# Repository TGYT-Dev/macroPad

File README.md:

# Images

<p align="left">
  
  <br>

</p>

# Bill of Materials
This should all be iuncluded in the macropad kit.

> 5x Cherry MX Switches
> 
> 1x Alps EC11E Rotary Encoder
> 
> 1x Seeeduino XIAO
> 
> 1x 0.91" 128x32 OLED Display
> 
> 4x M3 screws

# Notes

This is my first hardware project and I hope It turns out well... ~waiting for a review and working on minor improvements in the meantime.~

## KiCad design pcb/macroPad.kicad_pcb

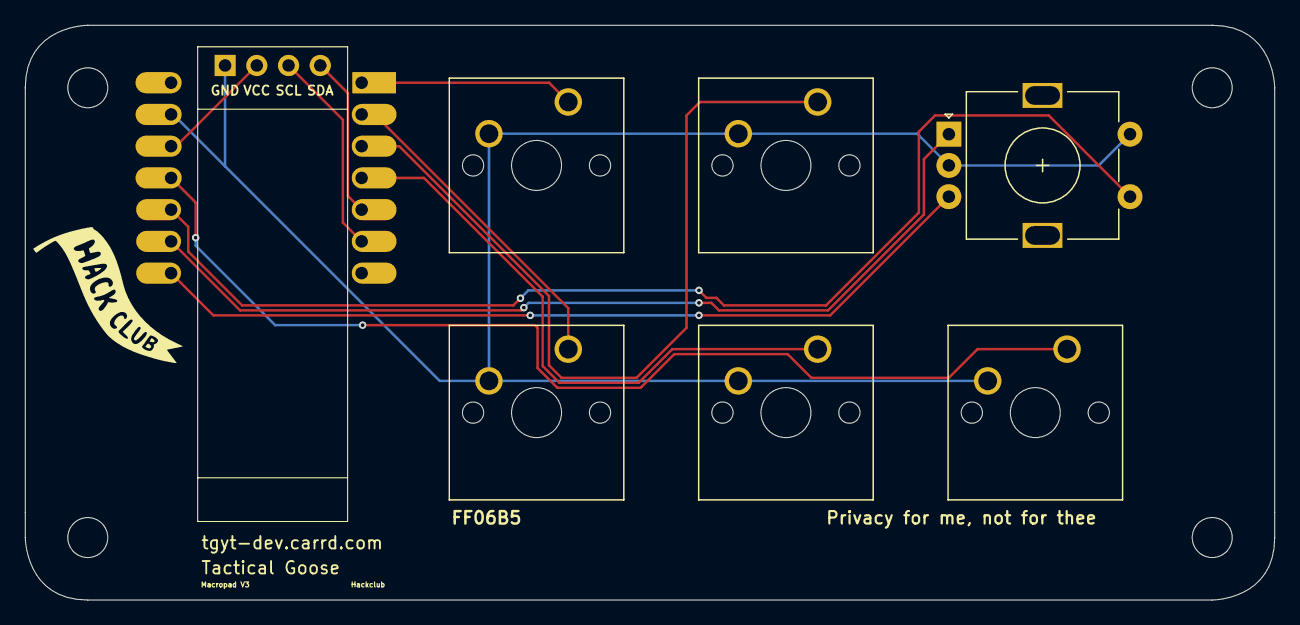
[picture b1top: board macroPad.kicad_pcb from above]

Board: 2 copper layers, 100.0 x 46.0 mm, 12 parts (1 on the bottom side), 11 nets.

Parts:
H1, H2, H3, H4: MountingHole; MountingHole_3.2mm_M3
SW1, SW2, SW3, SW4, SW5: SW_Push; SW_Cherry_MX_1.00u_PCB
SW6: RotaryEncoder_Switch; RotaryEncoder_Alps_EC11E-Switch_Vertical_H20mm
U1: MOUDLE-SEEEDUINO-XIAO; XIAO-Generic-Hybrid-14P-2.54-21X17.8MM
U2: ER_OLEDM0.91_1x-I2C; SSD1306-0.91-OLED-4pin-128x32

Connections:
GND: SW1.2, SW2.2, SW3.2, SW4.2, SW5.2 (2_2), SW6.C, SW6.S2, U1.13 (GND), U2.1 (GND)
unnamed: U1.12 (3V3), U2.2 (VCC)
unnamed: SW1.1, U1.1 (PA02_A0_D0)
unnamed: SW2.1, U1.2 (PA4_A1_D1)
unnamed: SW6.S1, U1.10 (PA5_A9_D9_MISO)
unnamed: SW6.A, U1.9 (PA7_A8_D8_SCK)
unnamed: U1.5 (PA8_A4_D4_SDA), U2.4 (SDA)
unnamed: U1.6 (PA9_A5_D5_SCL), U2.3 (SCL)
unnamed: SW3.1, U1.3 (PA10_A2_D2)
unnamed: SW4.1, U1.4 (PA11_A3_D3)
unnamed: SW6.B, U1.8 (PB09_A7_D7_RX)

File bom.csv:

"Id";"Designator";"Footprint";"Quantity";"Designation";"Supplier and ref";
1;"SW1, SW2, SW3, SW4, SW5";"SW_Cherry_MX_1.00u_PCB";5;"SW_Push";;;
2;"SW6";"RotaryEncoder_Alps_EC11E-Switch_Vertical_H20mm";1;"RotaryEncoder_Switch";;;
3;"U1";"XIAO-Generic-Hybrid-14P-2.54-21X17.8MM";1;"MOUDLE-SEEEDUINO-XIAO";;;
4;"U2";"SSD1306-0.91-OLED-4pin-128x32";1;"ER_OLEDM0.91_1x-I2C";;;
